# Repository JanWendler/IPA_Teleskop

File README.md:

#IPA Teleskop

This Project was my final Project in my apprenticeship as an Electronic Engineer
The goal was to measure the temperature and humidity infront of a teleskop lense to determ the dew point. If the temperature go to close to the actual dew point, an alarm will start.

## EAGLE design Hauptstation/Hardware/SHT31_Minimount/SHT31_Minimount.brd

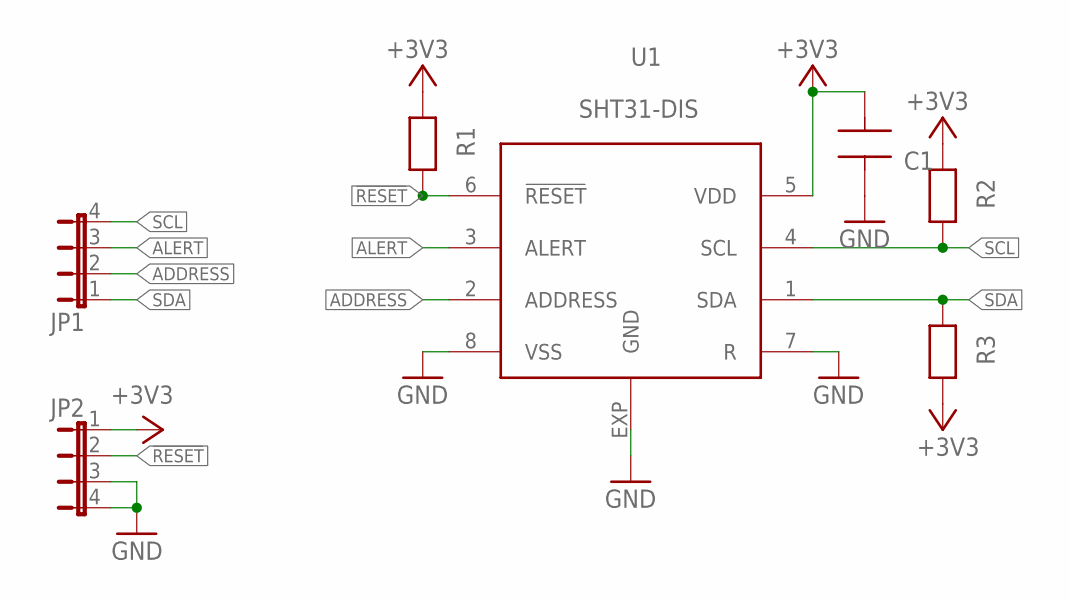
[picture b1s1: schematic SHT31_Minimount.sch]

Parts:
C1: C0603; 0603
JP1, JP2: JP4E; JP4
R1, R2, R3: R0603; 0603
U1: SHT31-DIS; DFN8-3X3

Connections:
!RESET!: JP2.2, R1.1, U1.6 (!RESET!)
+3V3: C1.1, JP2.1, R1.2, R2.2, R3.1, U1.5 (VDD)
ADDRESS: JP1.2, U1.2 (ADDRESS)
ALERT: JP1.3, U1.3 (ALERT)
GND: C1.2, JP2.3, JP2.4, U1.7 (R), U1.8 (VSS), U1.EXP (GND)
SCL: JP1.4, R2.1, U1.4 (SCL)
SDA: JP1.1, R3.2, U1.1 (SDA)

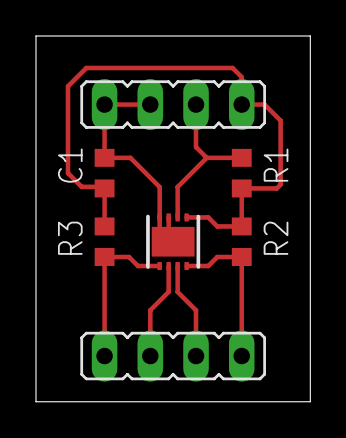
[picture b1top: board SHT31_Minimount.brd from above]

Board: 2 copper layers, 15.2 x 20.3 mm, 7 parts (0 on the bottom side), 7 nets.

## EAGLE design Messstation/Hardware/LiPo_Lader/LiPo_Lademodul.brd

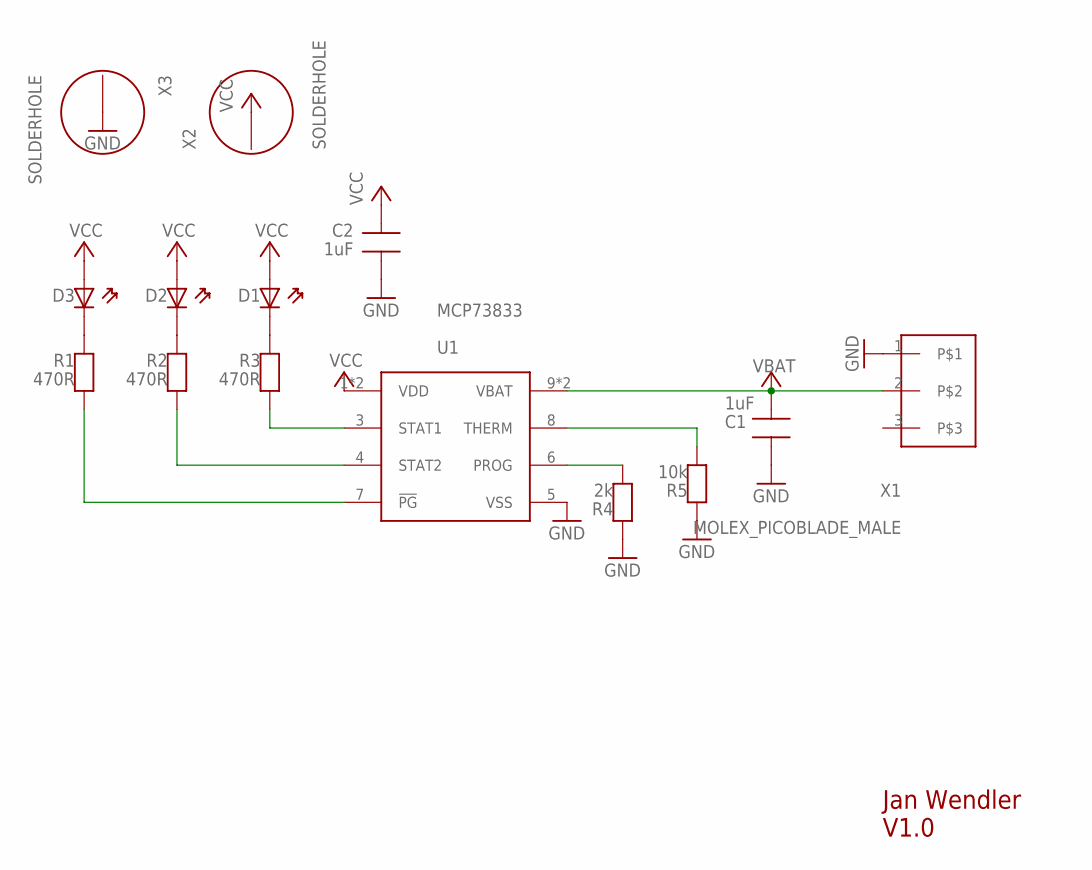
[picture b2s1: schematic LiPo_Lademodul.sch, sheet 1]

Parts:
C1, C2: 1uF; 0603
D1, D2, D3: D0603; 0603
R1, R2, R3: 470R; 0603
R4: 2k; 0603
R5: 10k; 0603
U1: MCP73833; MSOP10
X1: MOLEX_PICOBLADE_MALE
X2, X3: SOLDERHOLE; HOLE_2MM

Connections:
GND: C1.2, C2.1, R4.1, R5.1, U1.5 (VSS), X1.1, X3.P$1
unnamed: D1.2 (KATHODE), R3.2
unnamed: D2.2 (KATHODE), R2.2
unnamed: D3.2 (KATHODE), R1.2
unnamed: R4.2, U1.6 (PROG)
unnamed: R5.2, U1.8 (THERM)
unnamed: R3.1, U1.3 (STAT1)
unnamed: R2.1, U1.4 (STAT2)
unnamed: R1.1, U1.7 (!PG!)
VBAT: C1.1, U1.9 (VBAT), U1.10 (VBAT), X1.2
VCC: C2.2, D1.1 (ANODE), D2.1 (ANODE), D3.1 (ANODE), U1.1 (VDD), U1.2 (VDD), X2.P$1

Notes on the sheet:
Jan Wendler V1.0

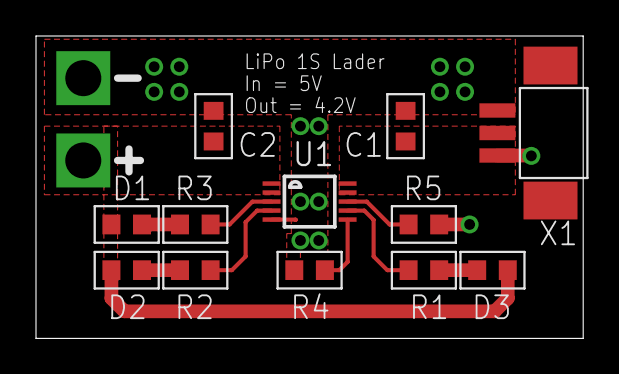
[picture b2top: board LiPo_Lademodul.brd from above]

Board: 2 copper layers, 30.4 x 16.8 mm, 14 parts (0 on the bottom side), 11 nets.

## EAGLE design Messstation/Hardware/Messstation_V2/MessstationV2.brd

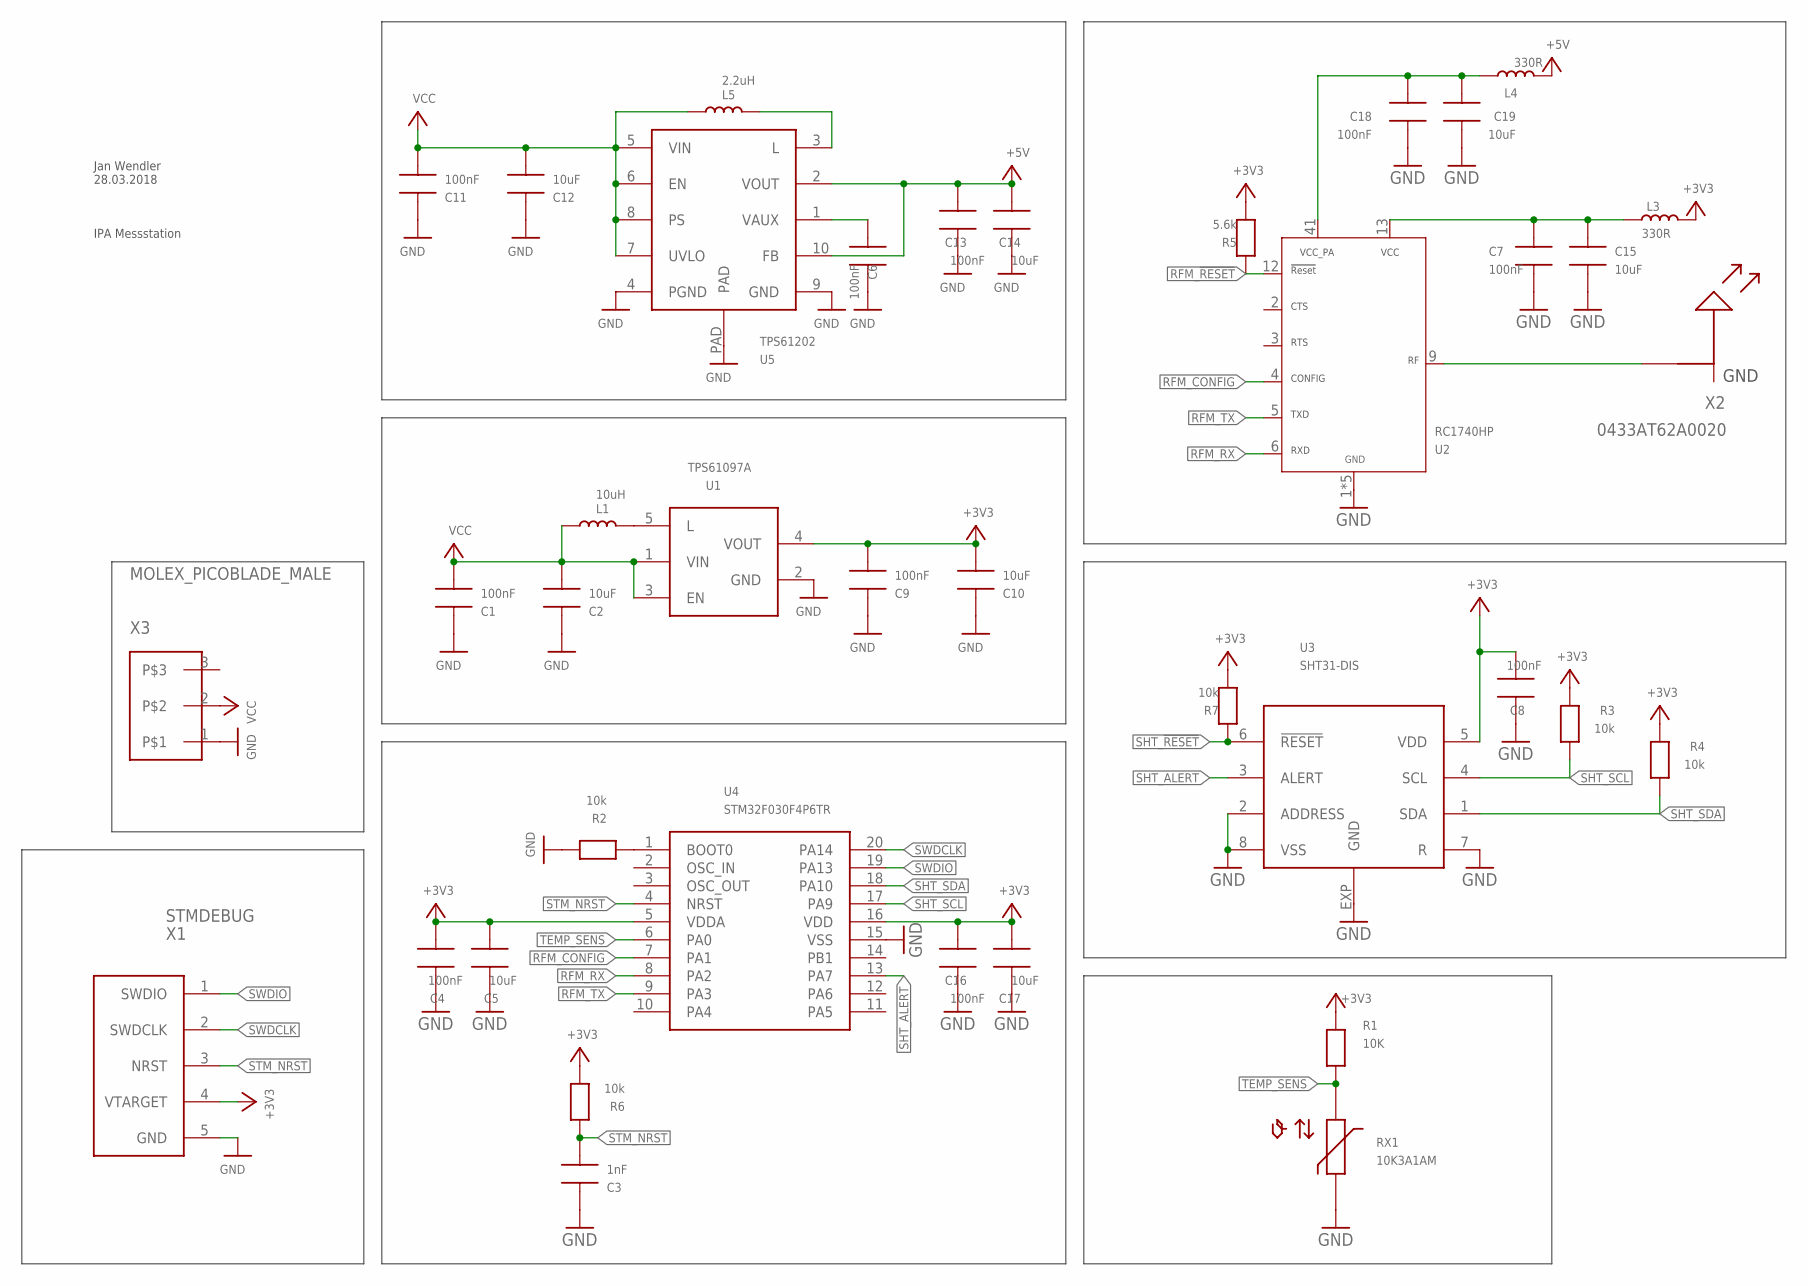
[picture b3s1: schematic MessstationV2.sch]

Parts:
C1, C4, C6, C7, C8, C9, C11, C13, C16, C18: 100nF; 0603
C2, C5, C10, C12, C14, C15, C17, C19: 10uF; 0603
C3: 1nF; 0603
L1: 10uH; L10
L3, L4: 330R; 0603
L5: 2.2uH; L2_2
R1: 10K; 0603
R2, R3, R4, R6, R7: 10k; 0603
R5: 5.6k; 0603
RX1: 10K3A1AM; TEMPSENS
U1: TPS61097A; SOT23-5L
U2: RC1740HP; RADIOCRAFTS_MODULE
U3: SHT31-DIS; DFN8-3X3
U4: STM32F030F4P6TR; TSSOP20
U5: TPS61202; VSON10
X1: STMDEBUG; STIFTLEISTE1X5
X2: 0433AT62A0020; ANTENNE_CON
X3: MOLEX_PICOBLADE_MALE

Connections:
+3V3: C4.1, C5.1, C8.1, C9.1, C10.1, C16.1, C17.1, L3.1, R1.2, R3.2, R4.2, R5.1, R6.1, R7.1, U1.4 (VOUT), U3.5 (VDD), U4.5 (VDDA), U4.16 (VDD), X1.4 (VTARGET)
+5V: C13.1, C14.1, L4.1, U5.2 (VOUT), U5.10 (FB)
GND: C1.2, C2.2, C3.2, C4.2, C5.2, C6.2, C7.2, C8.2, C9.2, C10.2, C11.2, C12.2, C13.2, C14.2, C15.2, C16.2, C17.2, C18.2, C19.2, R2.2, RX1.P$3, U1.2 (GND), U2.1 (GND), U2.7 (GND), U2.8 (GND), U2.10 (GND), U2.14 (GND), U3.2 (ADDRESS), U3.7 (R), U3.8 (VSS), U3.EXP (GND), U4.15 (VSS), U5.4 (PGND), U5.9 (GND), U5.PAD, X1.5 (GND), X3.1
unnamed: R2.1, U4.1 (BOOT0)
unnamed: L1.P$1, U1.5 (L)
unnamed: U2.9 (RF), X2.P$1
unnamed: C6.1, U5.1 (VAUX)
unnamed: C7.1, C15.1, L3.2, U2.13 (VCC)
unnamed: L5.P$1, U5.3 (L)
unnamed: C18.1, C19.1, L4.2, U2.41 (VCC_PA)
RFM_!RESET!: R5.2, U2.12 (!RESET!)
RFM_CONFIG: U2.4 (CONFIG), U4.7 (PA1)
RFM_RX: U2.6 (RXD), U4.8 (PA2)
RFM_TX: U2.5 (TXD), U4.9 (PA3)
SHT_!RESET!: R7.2, U3.6 (!RESET!)
SHT_ALERT: U3.3 (ALERT), U4.13 (PA7)
SHT_SCL: R3.1, U3.4 (SCL), U4.17 (PA9)
SHT_SDA: R4.1, U3.1 (SDA), U4.18 (PA10)
STM_NRST: C3.1, R6.2, U4.4 (NRST), X1.3 (NRST)
SWDCLK: U4.20 (PA14), X1.2 (SWDCLK)
SWDIO: U4.19 (PA13), X1.1 (SWDIO)
TEMP_SENS: R1.1, RX1.P$4, U4.6 (PA0)
VCC: C1.1, C2.1, C11.1, C12.1, L1.P$2, L5.P$2, U1.1 (VIN), U1.3 (EN), U5.5 (VIN), U5.6 (EN), U5.7 (UVLO), U5.8 (PS), X3.2

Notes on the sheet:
Jan Wendler 28.03.2018
IPA Messstation

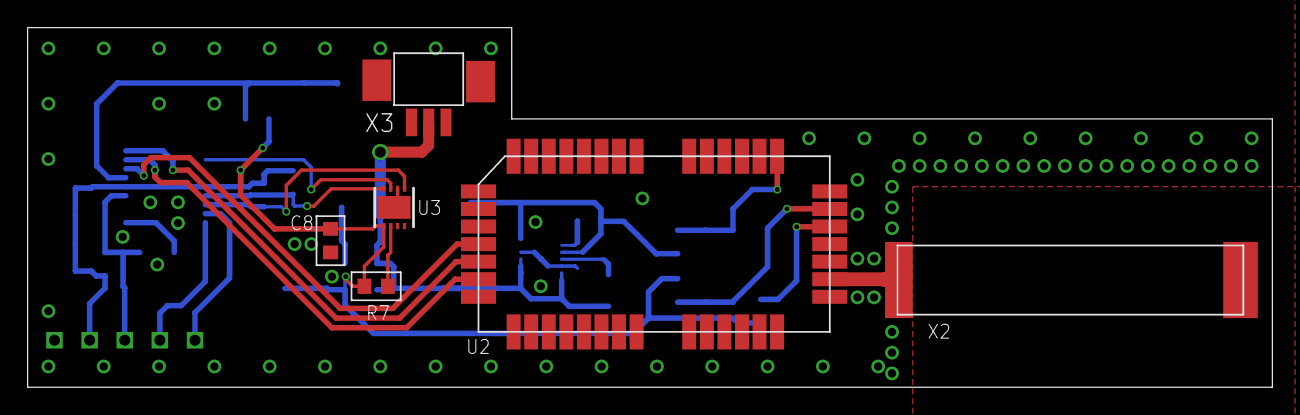
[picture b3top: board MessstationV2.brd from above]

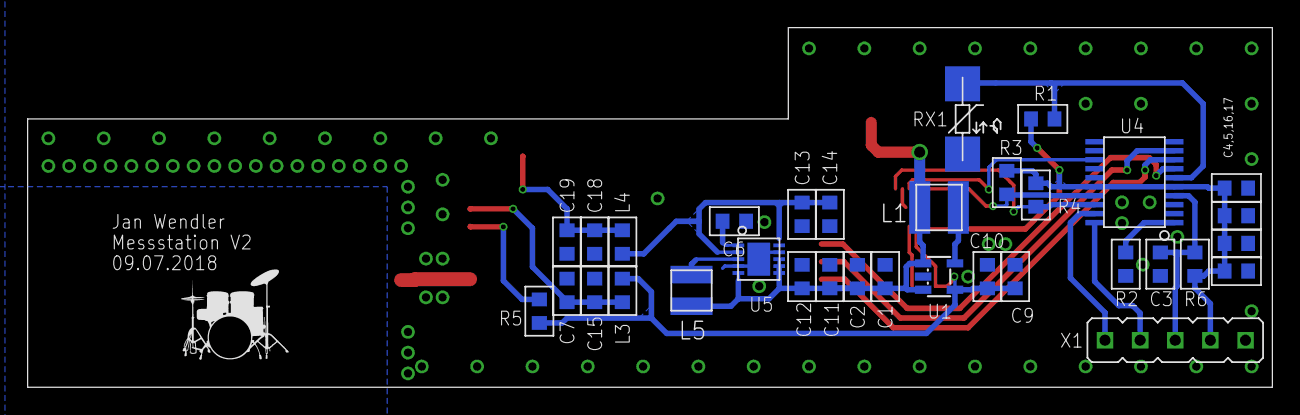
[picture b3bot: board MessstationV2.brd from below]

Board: 2 copper layers, 90.0 x 26.0 mm, 39 parts (33 on the bottom side), 23 nets.

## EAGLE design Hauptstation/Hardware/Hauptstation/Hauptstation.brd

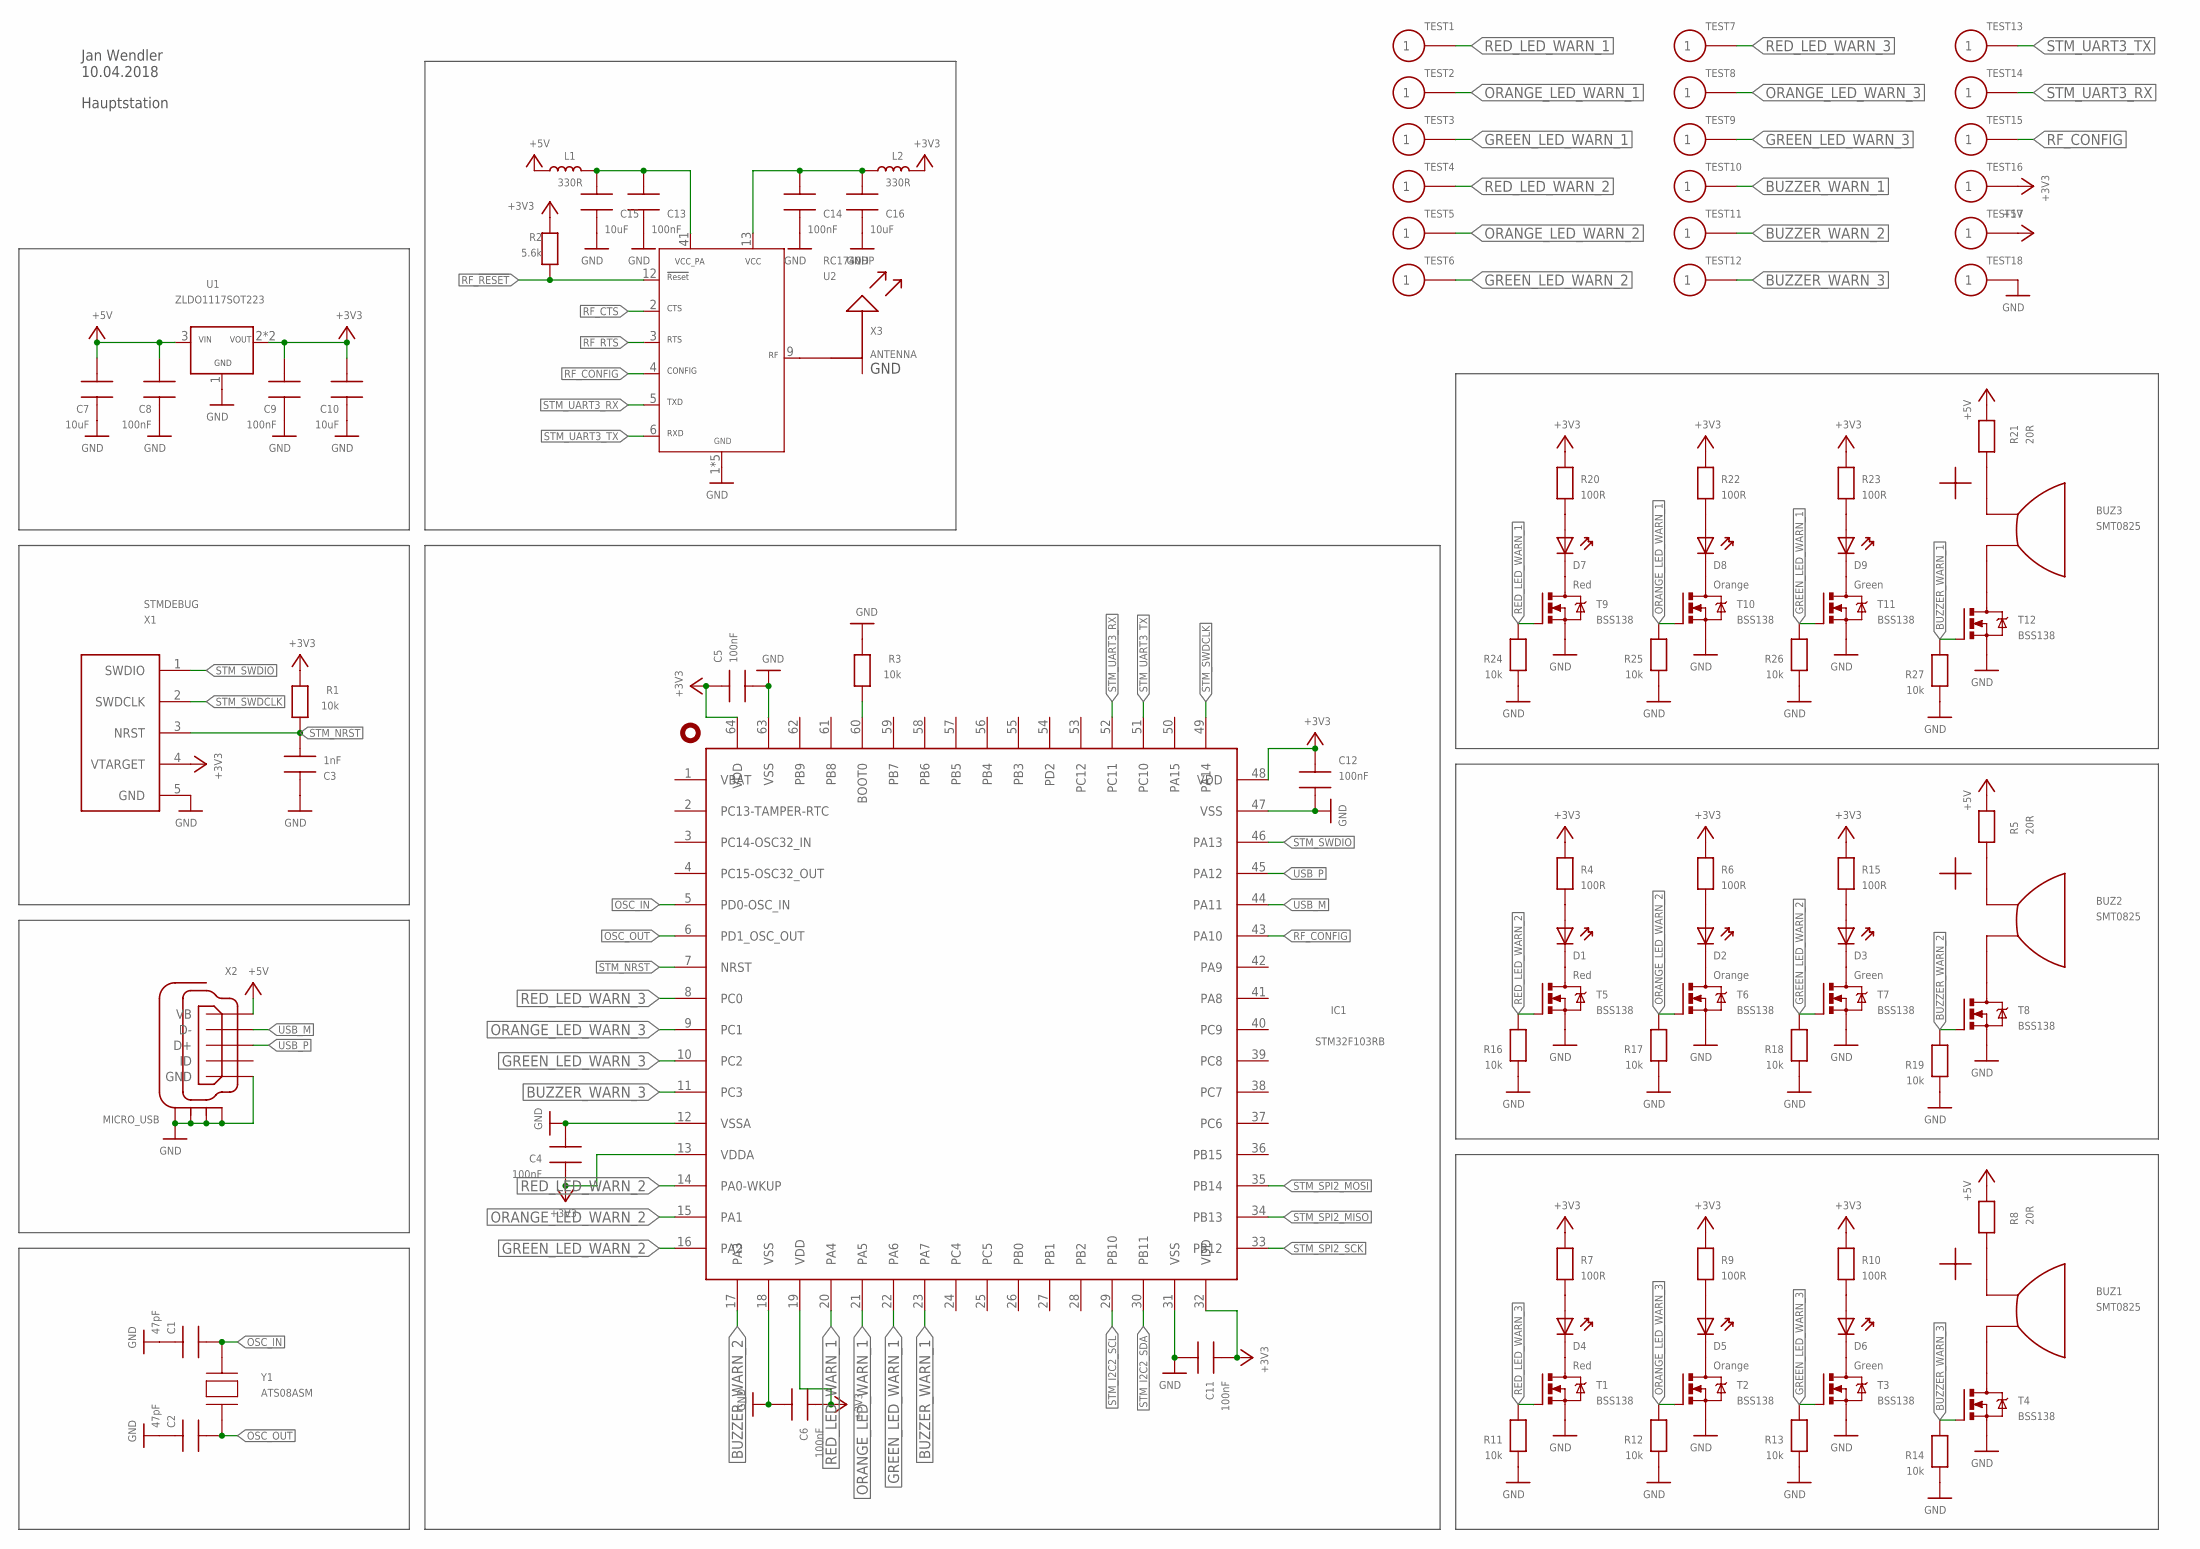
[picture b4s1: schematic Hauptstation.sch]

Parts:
BUZ1, BUZ2, BUZ3: SMT0825
C1, C2: 47pF; 0603
C3: 1nF; 0603
C4, C5, C6, C8, C9, C11, C12, C13, C14: 100nF; 0603
C7, C10, C15, C16: 10uF; 0603
D1, D4, D7: Red; 0603
D2, D5, D8: Orange; 0603
D3, D6, D9: Green; 0603
IC1: STM32F103RB; LQFP64
L1, L2: 330R; 0603
R1, R3, R11, R12, R13, R14, R16, R17, R18, R19, R24, R25, R26, R27: 10k; 0603
R2: 5.6k; 0603
R4, R6, R7, R9, R10, R15, R20, R22, R23: 100R; 0603
R5, R8, R21: 20R; 0603
T1, T2, T3, T4, T5, T6, T7, T8, T9, T10, T11, T12: BSS138; SOT23
TEST1, TEST2, TEST3, TEST4, TEST5, TEST6, TEST7, TEST8, TEST9, TEST10, TEST11, TEST12, TEST13, TEST14, TEST15, TEST16, TEST17, TEST18: TESTPIN
U1: ZLDO1117SOT223; SOT223
U2: RC1740HP; RADIOCRAFTS_MODULE
X1: STMDEBUG; STIFTLEISTE1X5
X2: MICRO_USB; MICRO-USB
X3: ANTENNA; ANTENNE_CON
Y1: ATS08ASM; HC49/US

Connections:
+3V3: C4.2, C5.2, C6.2, C9.1, C10.1, C11.2, C12.2, IC1.13 (VDDA), IC1.19 (VDD), IC1.32 (VDD), IC1.48 (VDD), IC1.64 (VDD), L2.1, R1.2, R2.2, R4.2, R6.2, R7.2, R9.2, R10.2, R15.2, R20.2, R22.2, R23.2, TEST16.1, U1.2 (VOUT), U1.PAD (VOUT), X1.4 (VTARGET)
+5V: C7.1, C8.1, L1.2, R5.2, R8.2, R21.2, TEST17.1, U1.3 (VIN), X2.1 (VB)
BUZZER_WARN_1: IC1.23 (PA7), R27.2, T12.1 (G), TEST10.1
BUZZER_WARN_2: IC1.17 (PA3), R19.2, T8.1 (G), TEST11.1
BUZZER_WARN_3: IC1.11 (PC3), R14.2, T4.1 (G), TEST12.1
GND: C1.2, C2.2, C3.1, C4.1, C5.1, C6.1, C7.2, C8.2, C9.2, C10.2, C11.1, C12.1, C13.2, C14.2, C15.2, C16.2, IC1.12 (VSSA), IC1.18 (VSS), IC1.31 (VSS), IC1.47 (VSS), IC1.63 (VSS), R3.2, R11.1, R12.1, R13.1, R14.1, R16.1, R17.1, R18.1, R19.1, R24.1, R25.1, R26.1, R27.1, T1.2 (S), T2.2 (S), T3.2 (S), T4.2 (S), T5.2 (S), T6.2 (S), T7.2 (S), T8.2 (S), T9.2 (S), T10.2 (S), T11.2 (S), T12.2 (S), TEST18.1, U1.1 (GND), U2.1 (GND), U2.7 (GND), U2.8 (GND), U2.10 (GND), U2.14 (GND), X1.5 (GND), X2.5 (GND), X2.GND1 (S1), X2.GND2 (S2), X2.GND3 (S3), X2.GND4 (S4)
GREEN_LED_WARN_1: IC1.22 (PA6), R26.2, T11.1 (G), TEST3.1
GREEN_LED_WARN_2: IC1.16 (PA2), R18.2, T7.1 (G), TEST6.1
GREEN_LED_WARN_3: IC1.10 (PC2), R13.2, T3.1 (G), TEST9.1
unnamed: U2.9 (RF), X3.P$1
unnamed: C13.1, C15.1, L1.1, U2.41 (VCC_PA)
unnamed: C14.1, C16.1, L2.2, U2.13 (VCC)
unnamed: D4.1 (ANODE), R7.1
unnamed: D5.1 (ANODE), R9.1
unnamed: IC1.60 (BOOT0), R3.1
unnamed: D6.1 (ANODE), R10.1
unnamed: D4.2 (KATHODE), T1.3 (D)
unnamed: D5.2 (KATHODE), T2.3 (D)
unnamed: D6.2 (KATHODE), T3.3 (D)
unnamed: BUZ1.+, R8.1
unnamed: BUZ1.-, T4.3 (D)
unnamed: D1.1 (ANODE), R4.1
unnamed: D2.1 (ANODE), R6.1
unnamed: D3.1 (ANODE), R15.1
unnamed: D1.2 (KATHODE), T5.3 (D)
unnamed: D2.2 (KATHODE), T6.3 (D)
unnamed: D3.2 (KATHODE), T7.3 (D)
unnamed: BUZ2.+, R5.1
unnamed: BUZ2.-, T8.3 (D)
unnamed: D7.1 (ANODE), R20.1
unnamed: D8.1 (ANODE), R22.1
unnamed: D9.1 (ANODE), R23.1
unnamed: D7.2 (KATHODE), T9.3 (D)
unnamed: D8.2 (KATHODE), T10.3 (D)
unnamed: D9.2 (KATHODE), T11.3 (D)
unnamed: BUZ3.+, R21.1
unnamed: BUZ3.-, T12.3 (D)
ORANGE_LED_WARN_1: IC1.21 (PA5), R25.2, T10.1 (G), TEST2.1
ORANGE_LED_WARN_2: IC1.15 (PA1), R17.2, T6.1 (G), TEST5.1
ORANGE_LED_WARN_3: IC1.9 (PC1), R12.2, T2.1 (G), TEST8.1
OSC_IN: C1.1, IC1.5 (PD0-OSC_IN), Y1.1
OSC_OUT: C2.1, IC1.6 (PD1_OSC_OUT), Y1.2
RED_LED_WARN_1: IC1.20 (PA4), R24.2, T9.1 (G), TEST1.1
RED_LED_WARN_2: IC1.14 (PA0-WKUP), R16.2, T5.1 (G), TEST4.1
RED_LED_WARN_3: IC1.8 (PC0), R11.2, T1.1 (G), TEST7.1
RF_!RESET!: R2.1, U2.12 (!RESET!)
RF_CONFIG: IC1.43 (PA10), TEST15.1, U2.4 (CONFIG)
RF_CTS: U2.2 (CTS)
RF_RTS: U2.3 (RTS)
STM_I2C2_SCL: IC1.29 (PB10)
STM_I2C2_SDA: IC1.30 (PB11)
STM_NRST: C3.2, IC1.7 (NRST), R1.1, X1.3 (NRST)
STM_SPI2_MISO: IC1.34 (PB13)
STM_SPI2_MOSI: IC1.35 (PB14)
STM_SPI2_SCK: IC1.33 (PB12)
STM_SWDCLK: IC1.49 (PA14), X1.2 (SWDCLK)
STM_SWDIO: IC1.46 (PA13), X1.1 (SWDIO)
STM_UART3_RX: IC1.52 (PC11), TEST14.1, U2.5 (TXD)
STM_UART3_TX: IC1.51 (PC10), TEST13.1, U2.6 (RXD)
USB_M: IC1.44 (PA11), X2.2 (D-)
USB_P: IC1.45 (PA12), X2.3 (D+)

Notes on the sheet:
Jan Wendler 10.04.2018
Hauptstation

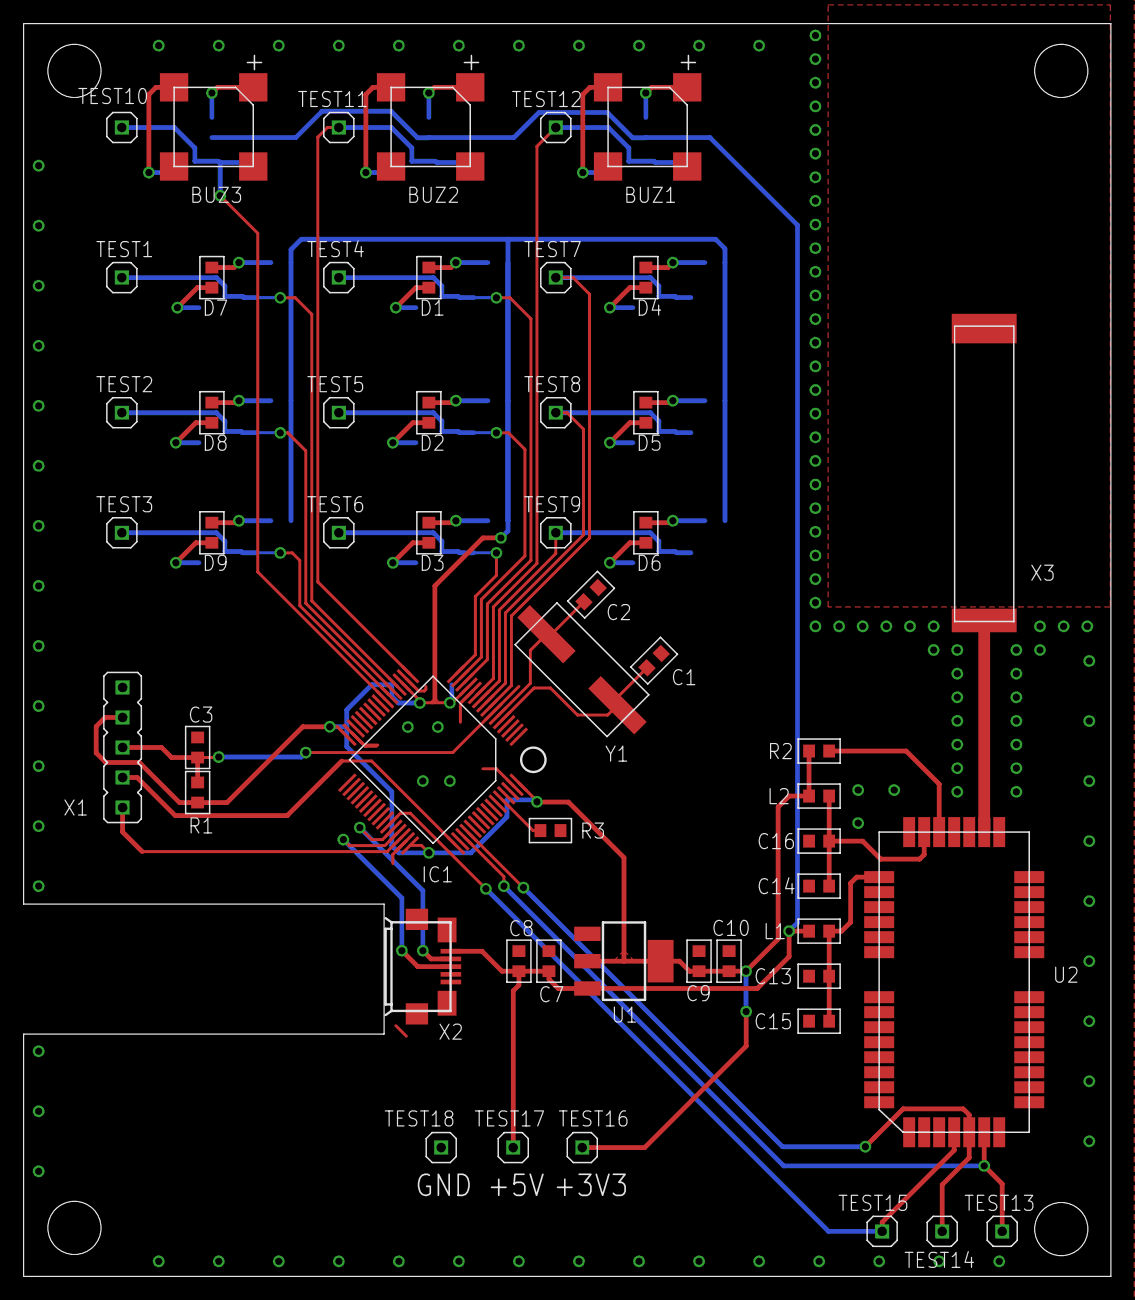
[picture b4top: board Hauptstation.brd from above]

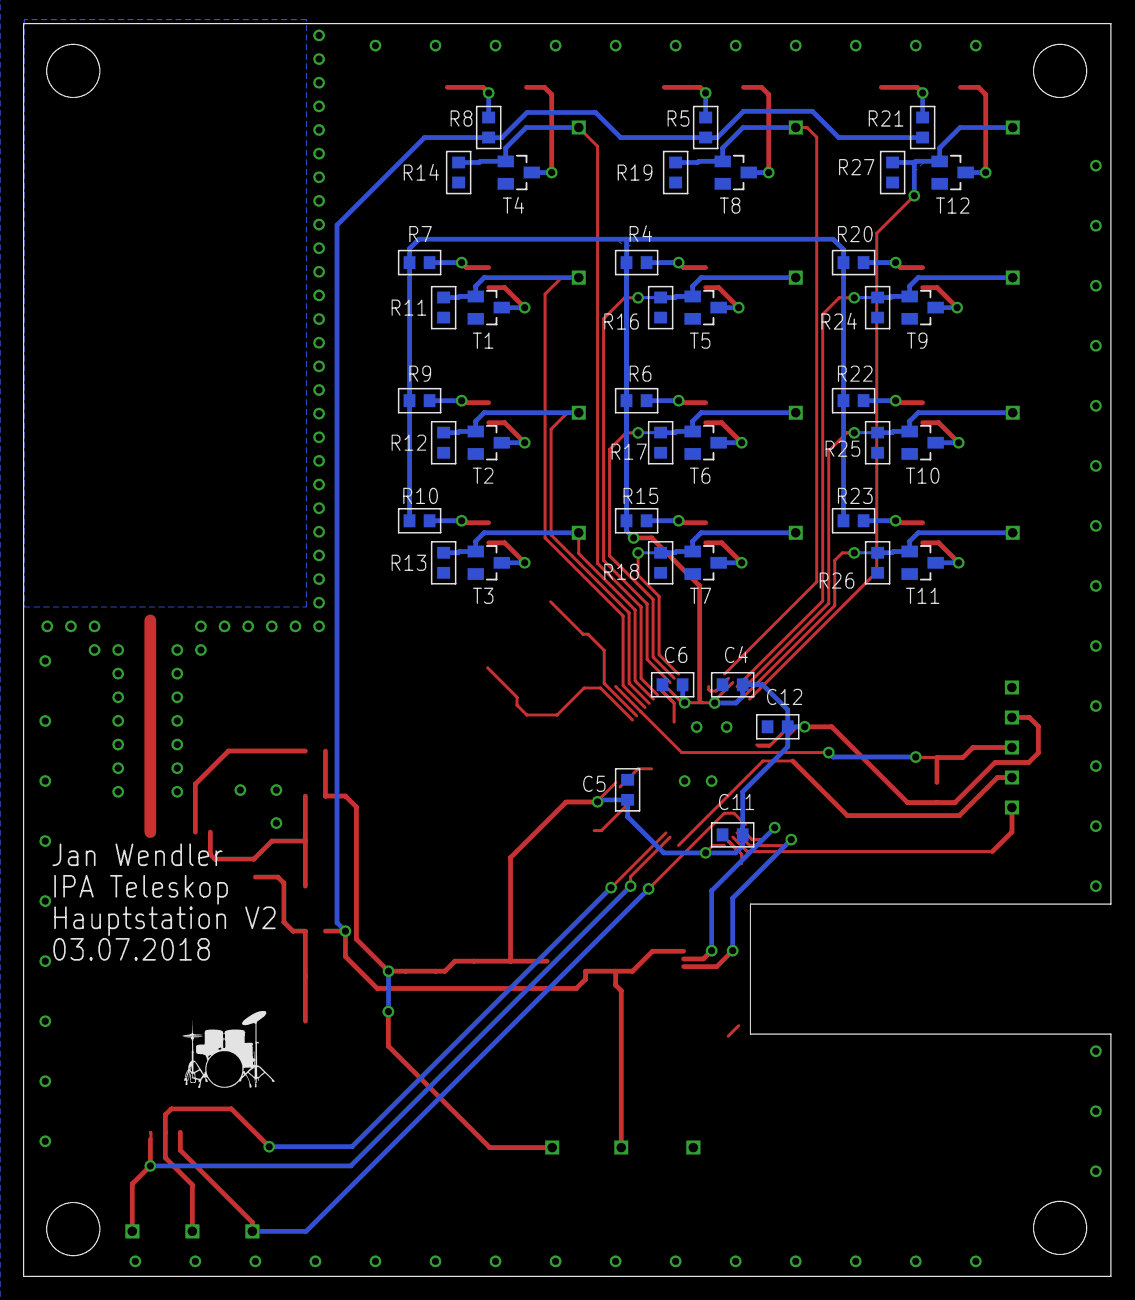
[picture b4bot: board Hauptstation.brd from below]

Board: 2 copper layers, 92.0 x 106.0 mm, 94 parts (41 on the bottom side), 54 nets.

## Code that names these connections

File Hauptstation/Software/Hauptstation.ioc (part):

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Mcu.Name=STM32F103R(8-B)Tx
Mcu.Package=LQFP64
Mcu.UserName=STM32F103RBTx
PA0-WKUP.GPIOParameters=GPIO_Label
PA0-WKUP.GPIO_Label=Warn10
PA0-WKUP.Signal=GPIO_Output
PA1.GPIOParameters=GPIO_Label
PA1.GPIO_Label=Warn11
PA1.Signal=GPIO_Output
PA10.GPIOParameters=GPIO_Label
PA10.GPIO_Label=RF_Config
PA10.Signal=GPIO_Output
PA13.Mode=Serial_Wire
PA13.Signal=SYS_JTMS-SWDIO
PA14.Mode=Serial_Wire
PA14.Signal=SYS_JTCK-SWCLK
PA2.GPIOParameters=GPIO_Label
PA2.GPIO_Label=Warn12
PA2.Signal=GPIO_Output
PA3.GPIOParameters=GPIO_Label
PA3.GPIO_Label=Wanr13
PA3.Signal=GPIO_Output
PA4.GPIOParameters=GPIO_Label
PA4.GPIO_Label=Warn14
PA4.Signal=GPIO_Output
PA5.GPIOParameters=GPIO_Label
PA5.GPIO_Label=Warn15
PA5.Signal=GPIO_Output
PA6.GPIOParameters=GPIO_Label
PA6.GPIO_Label=Warn16
PA6.Signal=GPIO_Output
PA7.GPIOParameters=GPIO_Label
PA7.GPIO_Label=Warn17
PA7.Signal=GPIO_Output
PA8.GPIOParameters=GPIO_Label
PA8.GPIO_Label=Warn18
PA8.Signal=GPIO_Output
PA9.GPIOParameters=GPIO_Label
PA9.GPIO_Label=Warn19
PA9.Signal=GPIO_Output
PB0.GPIOParameters=GPIO_Label
PB0.GPIO_Label=Warn30
PB0.Signal=GPIO_Output
PB1.GPIOParameters=GPIO_Label
PB1.GPIO_Label=Warn31
PB1.Signal=GPIO_Output
PB10.GPIOParameters=GPIO_Label
PB10.GPIO_Label=Warn33
PB10.Mode=I2C
PB10.Signal=I2C2_SCL
PB11.GPIOParameters=GPIO_Label
PB11.GPIO_Label=Warn34
PB11.Mode=I2C
PB11.Signal=I2C2_SDA
PB13.Mode=Full_Duplex_Master
PB13.Signal=SPI2_SCK
PB14.Mode=Full_Duplex_Master
PB14.Signal=SPI2_MISO
PB15.Mode=Full_Duplex_Master
PB15.Signal=SPI2_MOSI
PB2.GPIOParameters=GPIO_Label
PB2.GPIO_Label=Warn32
PB2.Signal=GPIO_Output
PB3.GPIOParameters=GPIO_Label
PB3.GPIO_Label=Warn33
PB3.Signal=GPIO_Output
PB4.GPIOParameters=GPIO_Label
PB4.GPIO_Label=Warn34
PB4.Signal=GPIO_Output
PB5.GPIOParameters=GPIO_Label
PB5.GPIO_Label=Warn35
PB5.Signal=GPIO_Output
PB6.GPIOParameters=GPIO_Label
PB6.GPIO_Label=Warn36
PB6.Signal=GPIO_Output
PB7.GPIOParameters=GPIO_Label
PB7.GPIO_Label=Warn37
PB7.Signal=GPIO_Output
PB8.GPIOParameters=GPIO_Label
PB8.GPIO_Label=Warn38
PB8.Signal=GPIO_Output
PB9.GPIOParameters=GPIO_Label
PB9.GPIO_Label=Warn39
PB9.Signal=GPIO_Output
PC0.GPIOParameters=GPIO_Label
PC0.GPIO_Label=Warn20
PC0.Signal=GPIO_Output
PC1.GPIOParameters=GPIO_Label
PC1.GPIO_Label=Warn21
PC1.Signal=GPIO_Output
PC10.Mode=Asynchronous
PC10.Signal=USART3_TX
PC11.Mode=Asynchronous
PC11.Signal=USART3_RX
PC2.GPIOParameters=GPIO_Label
PC2.GPIO_Label=Warn22
PC2.Signal=GPIO_Output
PC3.GPIOParameters=GPIO_Label
PC3.GPIO_Label=Warn23
PC3.Signal=GPIO_Output
PC4.GPIOParameters=GPIO_Label
PC4.GPIO_Label=Warn24
PC4.Signal=GPIO_Output
PC5.GPIOParameters=GPIO_Label
PC5.GPIO_Label=Warn25
PC5.Signal=GPIO_Output
PC6.GPIOParameters=GPIO_Label
PC6.GPIO_Label=Warn26
PC6.Signal=GPIO_Output
PC7.GPIOParameters=GPIO_Label
PC7.GPIO_Label=Warn27
PC7.Signal=GPIO_Output
PC8.GPIOParameters=GPIO_Label
PC8.GPIO_Label=Warn28
PC8.Signal=GPIO_Output
PC9.GPIOParameters=GPIO_Label
PC9.GPIO_Label=Warn29
PC9.Signal=GPIO_Output
PD0-OSC_IN.Mode=HSE-External-Oscillator
PD0-OSC_IN.Signal=RCC_OSC_IN
PD1-OSC_OUT.Mode=HSE-External-Oscillator
PD1-OSC_OUT.Signal=RCC_OSC_OUT
RCC.HSEState=RCC_HSE_ON
RCC.SYSCLKFreq_VALUE=72000000
RCC.SYSCLKSource=RCC_SYSCLKSOURCE_PLLCLK
board=Hauptstation

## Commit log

2018-08-09 added README
